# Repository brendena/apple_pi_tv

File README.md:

# apple pi tv
The goal is to make a replacement board for the apple tv using a raspberry pi CM4

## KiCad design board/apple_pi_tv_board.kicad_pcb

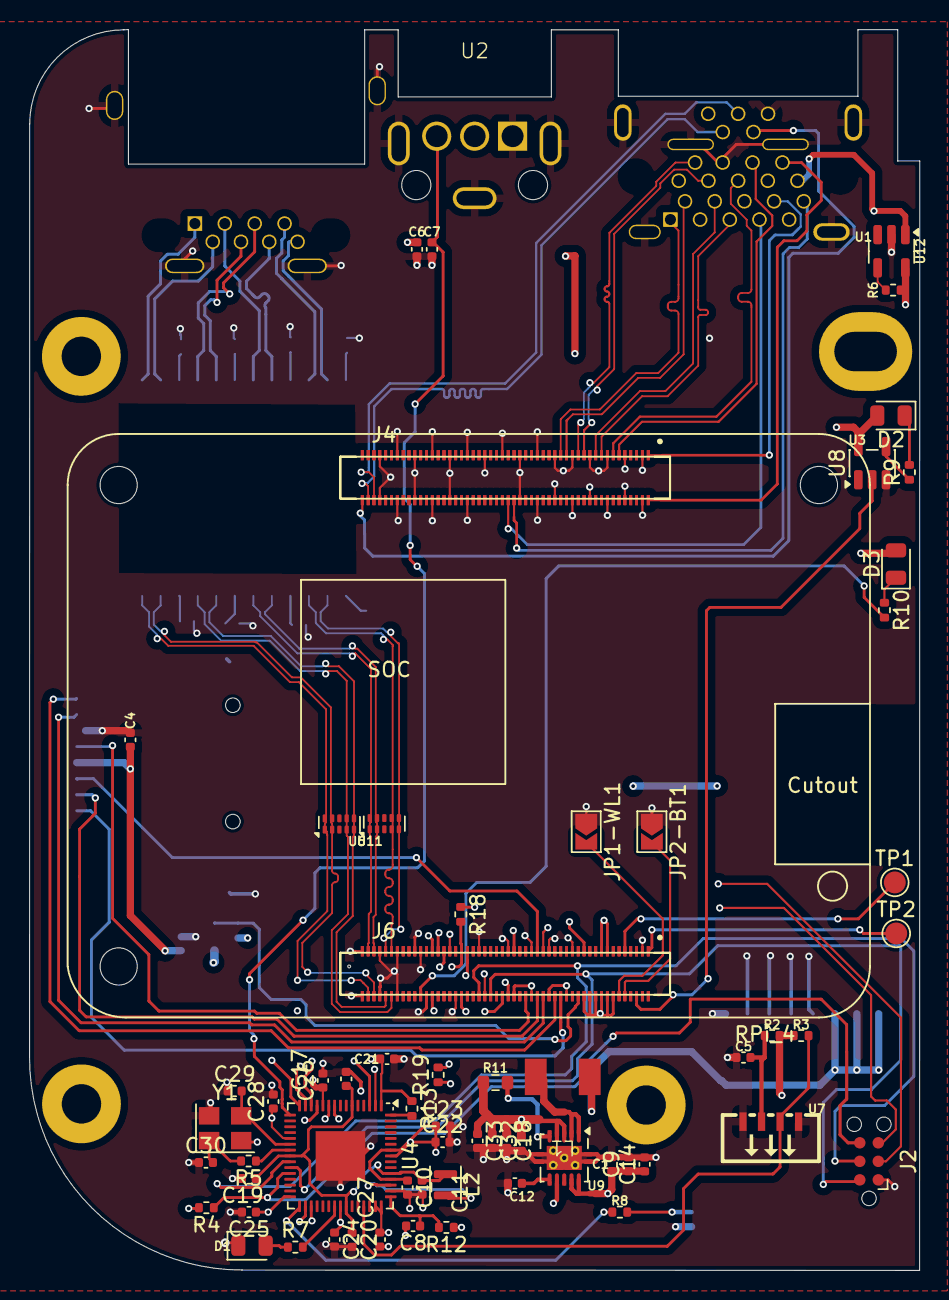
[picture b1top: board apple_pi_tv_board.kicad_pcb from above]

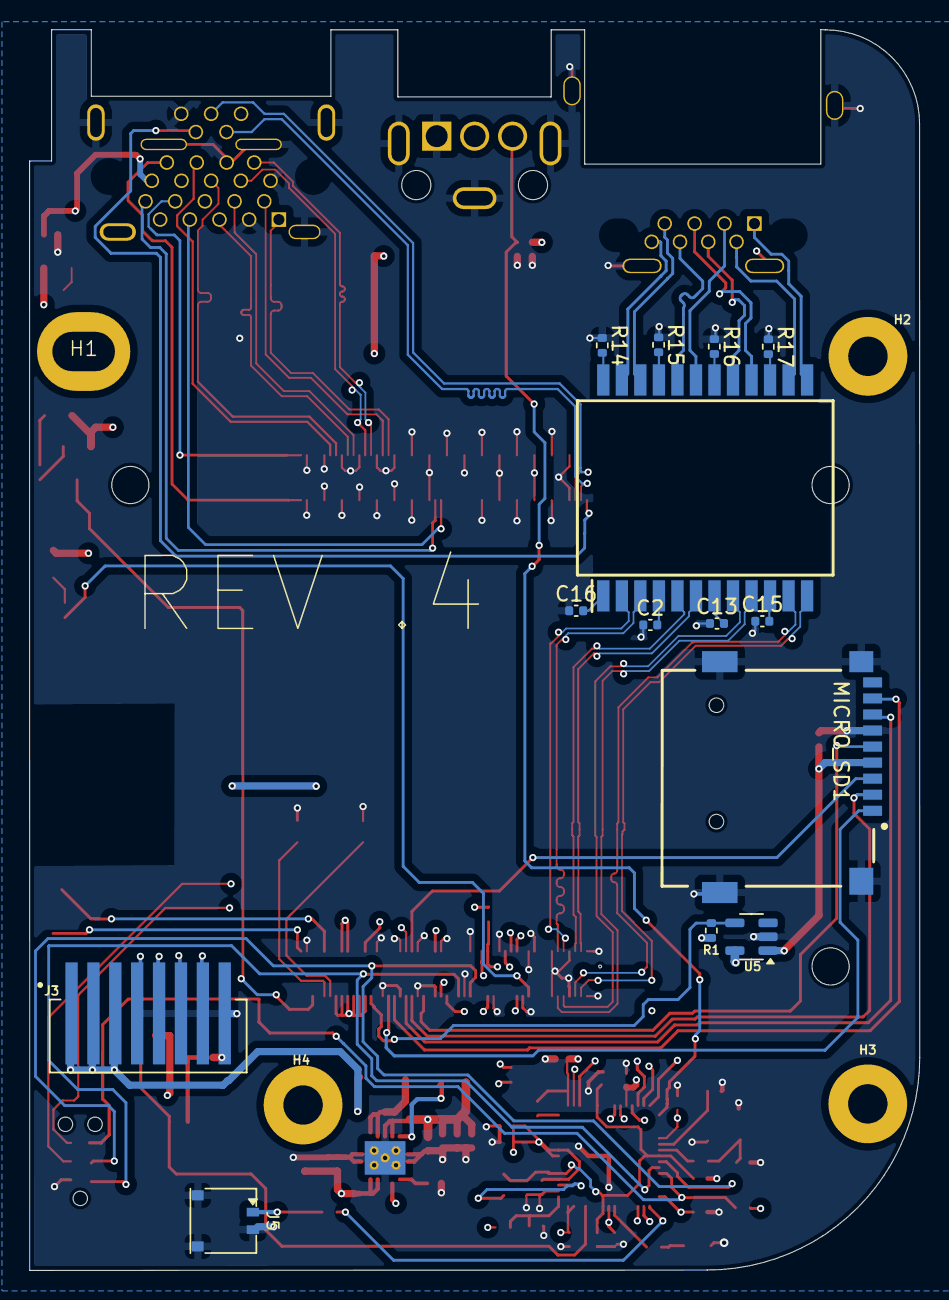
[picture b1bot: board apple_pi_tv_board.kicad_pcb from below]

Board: 4 copper layers, 61.0 x 85.1 mm, 84 parts (18 on the bottom side), 93 nets.

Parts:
C1, C4, C9, C14: 10u; C_0402_1005Metric
C2, C13, C15, C16: 0.1uf; C_0402_1005Metric
C3, C8, C10, C11, C18, C19: 4.7u; C_0402_1005Metric
C5: 2.2u; C_0402_1005Metric
C6, C17, C20, C21, C22, C23, C24, C25, C26, C27, C28: 100n; C_0402_1005Metric
C7: 30pF; C_0402_1005Metric
C12: 8.2nf; C_0402_1005Metric
C29, C30: 15pF; C_0402_1005Metric
C32, C33: 22u; C_0402_1005Metric
D1: GREEN; LED_0805_2012Metric
D2, D3: LED_Small; LED_0805_2012Metric
H1: MountingHole; ExtendedMountingHole
H2, H3, H4: MountingHole; MountingHole_2.7mm_Pad
J1: RJ45_Shielded; apple_tv_ethernet
J2: Dev_port; Tag-Connect_TC2030-IDC-NL_2x03_P1.27mm_Vertical
J3: 5-1775444-8; TE_5-1775444-8
J4, J6: DF40C-100DS-0.4V_51_; HIROSE_DF40C-100DS-0.4V_51_
J5: HDGC1202WR-S-2P; HDGC1202WR-S-02P
JP1-WL1, JP2-BT1: SolderJumper_2_Open; SolderJumper-2_P1.3mm_Open_TrianglePad1.0x1.5mm
L1: 1uH; MDA4020
L2: 3.3u; L_Murata_DFE201610P
MICRO_SD1: TF-01A
R1, R6: 12k 1%; R_0402_1005Metric
R2, R8, R18, R19: 220R; R_0402_1005Metric
R3, R4: 10k; R_0402_1005Metric
R5, R9, R10: 1k; R_0402_1005Metric
R7: 10K R; R_0402_1005Metric
R11: 100K; R_0603_1608Metric
R12: 33; R_0402_1005Metric
R13: 10K; R_0402_1005Metric
R14, R15, R16, R17: 75; R_0402_1005Metric
T1: H5007NL; SOIC127P1600X551-24N
TP1: RUN_PG; TestPoint_Pad_D1.5mm
TP2: Extrst; TestPoint_Pad_D1.5mm
U1: HDMI/USB; apple_tv_hdmi_usb
U2: apple tv tos link; apple_tv_tos_link
U3: RPi_4; RPI-CM4
U4: RP2354A; QFN-60-1EP_7x7mm_P0.4mm_EP3.4x3.4mm
U5, U12: RT9742GGJ5; SOT-23-5
U6, U11: TPD4EUSB30; USON-10_2.5x1.0mm_P0.5mm
U7: IRM-V838M3-C/TR1; OPTO-SMD_IRM-V838M3-C-TR1
U8: 74LVC1G07; SOT-23-5
U9: TPS61232DRC; Texas_S-PVSON-N10_ThermalVias
Y1: ABM8-272-T3; Crystal_SMD_3225-4Pin_3.2x2.5mm

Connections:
+1V1: C11.1, C17.1, C19.1, C20.1, L2.1, U4.6 (DVDD), U4.23 (DVDD), U4.39 (DVDD), U4.50 (VREG_FB)
+3V3: C6.1, C10.1, C21.1, C22.1, C23.1, C24.1, C25.1, C26.1, C27.1, C28.1, D2.2 (A), D3.2 (A), R1.1, R2.1, R3.1, R4.2, R12.1, R13.1, R18.1, R19.1, U2.2 (VCC), U3.78 (GPIO_VREF), U3.84 (CM4_3.3V(OUTPUT)), U3.86 (CM4_3.3V(OUTPUT)), U4.1 (IOVDD), U4.11 (IOVDD), U4.20 (IOVDD), U4.30 (IOVDD), U4.38 (IOVDD), U4.44 (ADC_AVDD), U4.45 (IOVDD), U4.49 (VREG_VIN), U4.53 (USB_OTP_VDD), U4.54 (QSPI_IOVDD), U5.5 (IN), U8.5 (VCC)
+5V: C3.1, C18.1, C32.1, C33.1, R6.1, R11.1, U3.77 (+5V(INPUT)), U3.79 (+5V(INPUT)), U3.81 (+5V(INPUT)), U3.83 (+5V(INPUT)), U3.85 (+5V(INPUT)), U3.87 (+5V(INPUT)), U9.3 (VOUT), U9.4 (VOUT), U9.7 (FB), U12.5 (IN)
/HDMI0_CEC: U1.13 (CEC), U3.151 (HDMI0_CEC)
/HDMI0_CK_N: U1.12 (CK-), U3.190 (HDMI0_CLK_N)
/HDMI0_CK_P: U1.10 (CK+), U3.188 (HDMI0_CLK_P)
/HDMI0_D0_N: U1.9 (D0-), U3.184 (HDMI0_TX0_N)
/HDMI0_D0_P: U1.7 (D0+), U3.182 (HDMI0_TX0_P)
/HDMI0_D1_N: U1.6 (D1-), U3.178 (HDMI0_TX1_N)
/HDMI0_D1_P: U1.4 (D1+), U3.176 (HDMI0_TX1_P)
/HDMI0_D2_N: U1.3 (D2-), U3.172 (HDMI0_TX2_N)
/HDMI0_D2_P: U1.1 (D2+), U3.170 (HDMI0_TX2_P)
/HDMI0_HOTPLUG: U1.19 (HPD/HEAC-), U3.153 (HDMI0_HOTPLUG)
/HDMI0_SCL: U1.15 (SCL), U3.200 (HDMI0_SCL)
/HDMI0_SDA: U1.16 (SDA), U3.199 (HDMI0_SDA)
/HDMI_PWR_ON: R6.2, U12.4 (EN)
/HDMI_RJ45_USB/HDMI_5v: U1.18 (+5V), U1.20 (VBUS), U12.1 (OUT)
/HDMI_RJ45_USB/MCT0: R14.2, T1.24 (MCT1)
/HDMI_RJ45_USB/MCT1: R15.2, T1.21 (MCT2)
/HDMI_RJ45_USB/MCT2: R16.2, T1.18 (MCT3)
/HDMI_RJ45_USB/MCT3: R17.2, T1.15 (MCT4)
/HDMI_RJ45_USB/MX0_N: J1.8, T1.23 (MX1+)
/HDMI_RJ45_USB/MX0_P: J1.7, T1.22 (MX1-)
/HDMI_RJ45_USB/MX1_N: J1.6, T1.20 (MX2+)
/HDMI_RJ45_USB/MX1_P: J1.3, T1.19 (MX2-)
/HDMI_RJ45_USB/MX2_N: J1.4, T1.17 (MX3+)
/HDMI_RJ45_USB/MX2_P: J1.5, T1.16 (MX3-)
/HDMI_RJ45_USB/MX3_N: J1.2, T1.14 (MX4+)
/HDMI_RJ45_USB/MX3_P: J1.1, T1.13 (MX4-)
/HDMI_RJ45_USB/SD_PWR: C4.1, MICRO_SD1.4 (VDD), U5.1 (OUT)
/I2S_CLK: U3.49 (GPIO18), U4.12 (GPIO8)
/I2S_LRCLK: U3.26 (GPIO19), U4.13 (GPIO9)
/I2S_OUT: U3.25 (GPIO21), U4.14 (GPIO10)
/PI_UART_TX: J2.3 (Pi_Tx), U3.51 (GPIO15)
/PI_eeprom_scl: R19.2, U3.35 (ID_SC), U4.10 (GPIO7)
/Pi_eeprom_sda: R18.2, U3.36 (ID_SD), U4.9 (GPIO6)
/Pico_TOSLINK_IR/PICO_LED: R7.2, U4.37 (GPIO25)
/Pico_TOSLINK_IR/Pico_blinky: R8.1, U4.31 (GPIO19)
/Pico_TOSLINK_IR/XTAL_IN: C29.2, U4.21 (XIN), Y1.3
/Pico_TOSLINK_IR/XTAL_O: C30.2, R5.2, Y1.1
/Pico_TOSLINK_IR/XTAL_OUT: R5.1, U4.22 (XOUT)
/Pico_TOSLINK_IR/toslink: C7.1, U2.3 (VIN), U4.16 (GPIO12)
/Pico_TOSLINK_IR/~RESET: J2.6 (RST), R4.1, U4.26 (RUN)
/Pico_hid_irq: U3.30 (GPIO6), U4.15 (GPIO11)
/Pico_scl: U3.28 (GPIO13), U4.33 (GPIO21)
/Pico_sda: U3.38 (GPIO11), U4.32 (GPIO20)
/Power/power in: C1.1, C9.1, C14.1, J3.1, J3.2, J3.3, L1.1, U9.9 (EN), U9.10 (VIN)
/SD_CLK: MICRO_SD1.5 (CLK), U3.57 (SD_CLK)
/SD_CMD: MICRO_SD1.3 (CMD), U3.62 (SD_CMD)
/SD_DAT0: MICRO_SD1.7 (DAT0), U3.63 (SD_DAT0)
/SD_DAT1: MICRO_SD1.8 (DAT1), U3.67 (SD_DAT1)
/SD_DAT2: MICRO_SD1.1 (DAT2), U3.69 (SD_DAT2)
/SD_DAT3: MICRO_SD1.2 (CD/DAT3), U3.61 (SD_DAT3)
/SD_PWR_ON: R1.2, U3.75 (SD_PWR_ON), U5.4 (EN)
/TRD0_N: T1.2 (TD1+), U3.10 (ETH_PAIR0_N), U11.5 (D2-)
/TRD0_P: T1.3 (TD1-), U3.12 (ETH_PAIR0_P), U11.4 (D2+)
/TRD1_N: T1.5 (TD2+), U3.6 (ETH_PAIR1_N), U11.2 (D1-)
/TRD1_P: T1.6 (TD2-), U3.4 (ETH_PAIR1_P), U11.1 (D1+)
/TRD2_N: T1.8 (TD3+), U3.9 (ETH_PAIR2_N), U6.5 (D2-)
/TRD2_P: T1.9 (TD3-), U3.11 (ETH_PAIR2_P), U6.4 (D2+)
/TRD3_N: T1.11 (TD4+), U3.5 (ETH_PAIR3_N), U6.2 (D1-)
/TRD3_P: T1.12 (TD4-), U3.3 (ETH_PAIR3_P), U6.1 (D1+)
/USB_D+: U1.21 (D+), U3.105 (USB_P)
/USB_D-: U1.22 (D-), U3.103 (USB_N)
/USB_ID: U1.23 (ID), U3.101 (USB_OTG_ID)
/pico_rx: U3.54 (GPIO4), U4.3 (GPIO1)
/pico_tx: J2.5 (Pico_Tx), U3.64 (SD_DAT5), U4.2 (GPIO0)
/swclk: J2.4 (SWCLK), U3.41 (GPIO25), U4.24 (SWCLK)
/swdio: J2.2 (SWD), U3.45 (GPIO24), U4.25 (SWDIO)
GND: C1.2, C2.1, C3.2, C4.2, C5.2, C6.2, C7.2, C8.2, C9.2, C10.2, C11.2, C12.2, C13.1, C14.2, C15.1, C16.1, C17.2, C18.2, C19.2, C20.2, C21.2, C22.2, C23.2, C24.2, C25.2, C26.2, C27.2, C28.2, C29.1, C30.1, C32.2, C33.2, D1.1 (K), J1.SH, J2.1 (GND), J3.4, J3.5, J3.6, J3.7, J3.8, J5.2, J5.MP, JP1-WL1.1 (A), JP2-BT1.1 (A), MICRO_SD1.6 (VSS), MICRO_SD1.MP1 (SHIELD), MICRO_SD1.MP2 (SHIELD), MICRO_SD1.MP3 (SHIELD), MICRO_SD1.MP4 (SHIELD), R14.1, R15.1, R16.1, R17.1, U1.2 (D2S), U1.5 (D1S), U1.8 (D0S), U1.11 (CKS), U1.17 (GND), U1.24 (GND), U1.25 (GND), U2.1 (GND), U2.4 (Case_GND), U3.1 (GND), U3.2 (GND), U3.7 (GND), U3.8 (GND), U3.13 (GND), U3.14 (GND), U3.20 (EEPROM_~WP), U3.22 (GND), U3.23 (GND), U3.32 (GND), U3.33 (GND), U3.42 (GND), U3.43 (GND), U3.52 (GND), U3.53 (GND), U3.59 (GND), U3.60 (GND), U3.65 (GND), U3.66 (GND), U3.71 (GND), U3.74 (GND), U3.98 (GND), U3.107 (GND), U3.108 (GND), U3.113 (GND), U3.114 (GND), U3.119 (GND), U3.120 (GND), U3.125 (GND), U3.126 (GND), U3.131 (GND), U3.132 (GND), U3.137 (GND), U3.138 (GND), U3.144 (GND), U3.150 (GND), U3.155 (GND), U3.156 (GND), U3.161 (GND), U3.162 (GND), U3.167 (GND), U3.168 (GND), U3.173 (GND), U3.174 (GND), U3.179 (GND), U3.180 (GND), U3.185 (GND), U3.186 (GND), U3.191 (GND), U3.192 (GND), U3.197 (GND), U3.198 (GND), U4.47 (VREG_PGND), U4.61 (GND), U5.2 (GND), U6.3 (GND), U6.8 (GND), U7.1 (GND), U7.4 (GND), U8.3 (GND), U9.11 (GND), U11.3 (GND), U11.8 (GND), U12.2 (GND), Y1.2, Y1.4
unnamed: D1.2 (A), R7.1
unnamed: D2.1 (K), R9.2
unnamed: D3.1 (K), R10.1
unnamed: J5.1, R8.2
unnamed: JP1-WL1.2 (B), U3.89 (WL_~DISABLE)
unnamed: JP2-BT1.2 (B), U3.91 (BT_~DISABLE)
unnamed: L1.2, U9.1 (SW), U9.2 (SW)
unnamed: R9.1, U8.4
unnamed: C16.2, T1.1 (TCT1)
unnamed: C2.2, T1.4 (TCT2)
unnamed: C13.2, T1.7 (TCT3)
unnamed: C15.2, T1.10 (TCT4)
unnamed: U3.95 (PI_LED_~PWR), U8.2
unnamed: R10.2, U3.21 (PI_~LED_ACTIVITY)
unnamed: TP1.1, U3.92 (RUN_PG)
unnamed: TP2.1, U3.100 (~EXTRST)
unnamed: R3.2, U4.42 (GPIO28_ADC2), U7.3 (OUT)
unnamed: R13.2, U4.60 (QSPI_SS)
unnamed: C8.1, R12.2, U4.46 (VREG_AVDD)
unnamed: L2.2, U4.48 (VREG_LX)
unnamed: C5.1, R2.2, U7.2 (VCC)
unnamed: R11.2, U9.5 (PG)
unnamed: C12.1, U9.6 (SS)

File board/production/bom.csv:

Designator,Footprint,Quantity,Value,LCSC Part #
"C1, C14, C4, C9",0402,4,10u,
"C10, C11, C19, C3, C8",0402,5,4.7u,
C12,0402,1,8.2n,
"C13, C15, C16, C2",0402,4,C_Small,
"C17, C20, C21, C22, C23, C24, C25, C26, C27, C28, C6",0402,11,100n,
"C29, C30",0402,2,15pF,C1555
C5,0402,1,2.2u,
C7,0402,1,30pF,
D1,0805,1,GREEN,C2297
"D2, D3",0805,2,LED_Small,
J2,MICRO_SD_MOLEX_503398-1892,1,Micro_SD_Card_Det,
J3,TE_5-1775444-8,1,5-1775444-8,
J5,BM02BSRSSTBLFSN,1,BM02B-ACHSS-GAN-TF,
L1,MDA4020,1,1uH,
L2,L_Murata_DFE201610P,1,3.3u,
"R1, R6",0402,2,12k 1%,
"R10, R9",0402,2,R,
R11,0603,1,100K,
R12,0402,1,33,
"R13, R3, R4",0402,3,10K,
"R14, R15, R16, R17",0402,4,75,
"R2, R8",0402,2,220R,
R5,0402,1,1k,
R7,0402,1,470R,
T1,SOIC127P1600X551-24N,1,H5007NL,
TP1,TestPoint_Pad_D1.5mm,1,RUN_PG,
TP2,TestPoint_Pad_D1.5mm,1,Extrst,
"U11, U6",USON-10_2.5x1.0mm_P0.5mm,2,TPD4EUSB30,
"U12, U5",SOT-23-5,2,RT9742GGJ5,
U4,QFN-60-1EP_7x7mm_P0.4mm_EP3.4x3.4mm,1,RP2354A,
U7,OPTO-SMD_IRM-V838M3-C-TR1,1,IRM-V838M3-C/TR1,
U8,SOT-23-5,1,74LVC1G07,
U9,Texas_S-PVSON-N10_ThermalVias,1,TPS61232DRC,
Y1,Crystal_SMD_3225-4Pin_3.2x2.5mm,1,ABM8-272-T3,C9002

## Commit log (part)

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2024-07-14 got it almost looking good
2024-07-27 added 3d models
2024-07-27 moved the parts slightly
2024-08-24 added the board
2024-09-18 added the ignore files
2024-09-18 started working on rev 2
2024-10-03 got v2 done
2025-09-10 worked on new version with rp2350
2025-09-13 updated most stuff, but i completely redid the diff pairs
2025-09-14 almost v0.3
2025-10-17 Create ProblemsBoard.md
    Error's found with rev .3 that need to be verified and changed in the next rev
2025-11-13 going to add the magnetic transformer which will messs a lot of stuff up
2025-12-07 started more ethernet adding stuff
2025-12-14 added the real micro sd card slot
2025-12-20 got the ethernet routed
2025-12-21 removed some via's
2025-12-23 made the cutout for the magnet isolater
2025-12-23 should be the last build
